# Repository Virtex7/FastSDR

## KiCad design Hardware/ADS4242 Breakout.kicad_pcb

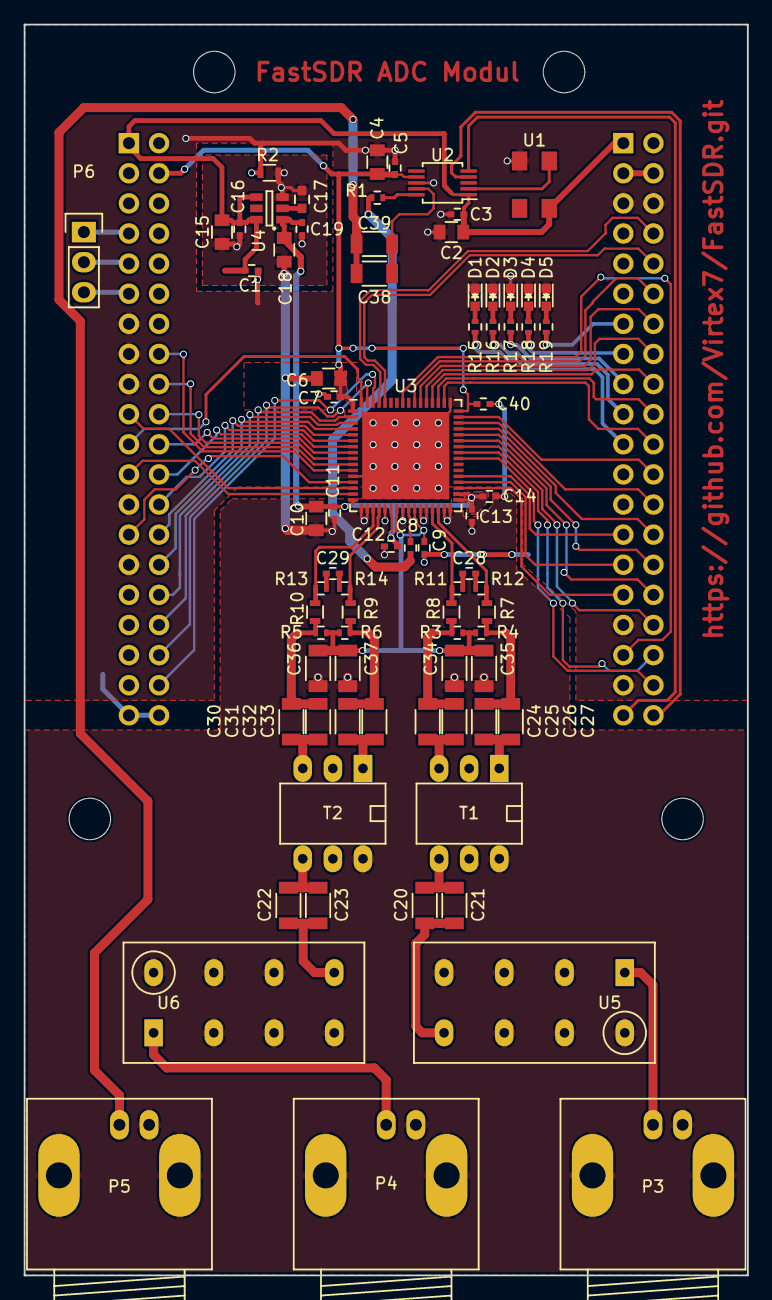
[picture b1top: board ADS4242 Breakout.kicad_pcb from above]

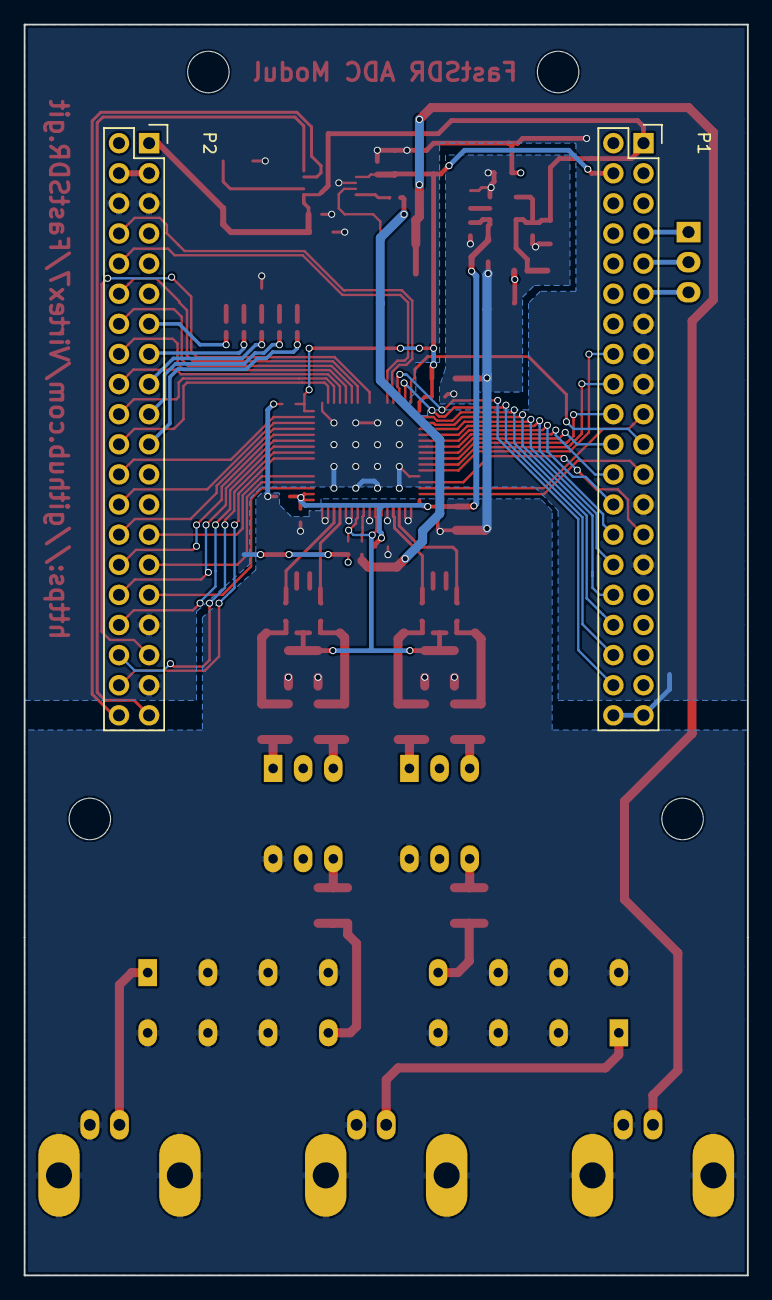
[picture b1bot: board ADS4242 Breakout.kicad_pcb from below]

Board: 2 copper layers, 61.0 x 105.5 mm, 82 parts (2 on the bottom side), 87 nets.

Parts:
C1, C3, C5, C7, C8, C9, C11, C12, C13, C14, C16, C19, C40: 100n; C_0402
C2, C4, C6, C10, C15, C18: 22u; C_0805
C17: 10n; C_0603
C20, C21, C22, C23, C24, C25, C26, C27, C30, C31, C32, C33, C34, C35, C36, C37, C38, C39: 47n; C_1206
C28, C29: 3,3p; C_0402
D1, D2, D3, D4, D5: LED; LED-0603
P1, P2: CONN_02X20; Socket_Strip_Straight_2x20
P3, P4, P5: BNC; BNC_Socket_TYCO-AMP_LargePads
P6: CONN_01X03; Pin_Header_Straight_1x03
P7, P8, P9, P10: CONN_01X01; MountingHole_3-5mm
R1: 49,9; R_0402
R2: 0; R_0603
R3, R4, R5, R6, R11, R12, R13, R14: 25; R_0402
R7, R8, R9, R10: 15; R_0603
R15, R16, R17, R18, R19: 1k; R_0402
T1, T2: T1-1T-X65; DIP-6__300_ELL
U1: FOX924B; FOX924
U2: SI5351A3; MSOP-10_3x3mm_Pitch0.5mm
U3: ADS4242; QFN-64-1EP_9x9mm_Pitch0.5mm
U4: TPS734xxDRV; SOT-23-6
U5, U6: PLP-21.4; A01-8

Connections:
1,8V: C4.1, C5.1, C6.1, C7.1, C40.1, P1.4, U2.7, U3.1, U3.48
3,3V: C1.1, C2.1, C3.1, C15.1, C16.1, P1.1, P2.1, U1.4, U2.1, U4.4, U4.6
5V: P2.3, P2.4
/CTL00: P2.31, U3.35
/CTL01: P2.29, U3.36
/CTL02: P2.27, U3.37
/CTL05: P2.21, R15.1
/CTL06: P2.19, R16.1
/CTL07: P2.17, R17.1
/CTL08: P2.15, R18.1
/CTL09: P2.13, R19.1
/DQ00: P2.38, U3.40
/DQ01: P2.36, U3.41
/DQ02: P2.34, U3.42
/DQ03: P2.32, U3.43
/DQ04: P2.30, U3.44
/DQ05: P2.28, U3.45
/DQ06: P2.26, U3.46
/DQ07: P2.24, U3.47
/DQ08: P2.22, U3.50
/DQ09: P2.20, U3.51
/DQ10: P2.18, U3.52
/DQ11: P2.16, U3.53
/DQ12: P2.14, U3.54
/DQ13: P2.12, U3.55
/DQ14: P2.10, U3.60
/DQ15: P2.8, U3.61
/DQ16: P1.38, U3.62
/DQ17: P1.36, U3.63
/DQ18: P1.34, U3.2
/DQ19: P1.32, U3.3
/DQ20: P1.30, U3.4
/DQ21: P1.28, U3.5
/DQ22: P1.26, U3.6
/DQ23: P1.24, U3.7
/DQ24: P1.22, U3.8
/DQ25: P1.20, U3.9
/DQ26: P1.18, U3.10
/DQ27: P1.16, U3.11
/I²C_SCL_FX3: P2.40, U2.4
/I²C_SDA_FX3: P2.39, U2.5
/PClk: P2.35, U3.57
/PMode_0: P1.11, P6.3
/PMode_1: P1.9, P6.2
/PMode_2: P1.7, P6.1
/Spi-Miso_Uart_TX: P1.21, U3.64
/Spi-Mosi_Uart-RX: P1.19, U3.14
/Spi-Sck_Uart-RTS: P1.27, U3.13
/Spi-Ssn_Uart-CTS: P1.23, U3.15
/VCM: C9.1, C34.1, C35.1, C36.1, C37.1, R3.2, R4.1, R5.2, R6.1, U3.23, U3.26
GND: C1.2, C2.2, C3.2, C4.2, C5.2, C9.2, D1.1, D2.1, D3.1, D4.1, D5.1, P1.13, P1.15, P1.17, P1.25, P1.29, P1.39, P1.40, P2.5, P2.6, P2.33, P2.37, R2.2, U1.2, U2.8, U3.12, U3.49, U3.65
GNDA: C6.2, C7.2, C10.2, C11.2, C12.2, C13.2, C14.2, C15.2, C16.2, C17.2, C18.2, C19.2, C34.2, C35.2, C36.2, C37.2, C40.2, P3.2, P4.2, P5.2, R2.1, T1.6, T2.6, U3.17, U3.18, U3.21, U3.24, U3.27, U3.28, U3.31, U3.32, U4.3, U5.2, U5.3, U5.4, U5.5, U5.6, U5.7, U6.2, U6.3, U6.4, U6.5, U6.6, U6.7
unnamed: C8.1, R1.1
unnamed: C8.2, U3.25
unnamed: C17.1, U4.2
unnamed: C20.1, C21.1, U5.8
unnamed: C20.2, C21.2, T1.4
unnamed: C22.1, C23.1, U6.8
unnamed: C22.2, C23.2, T2.4
unnamed: C24.1, C25.1, T1.3
unnamed: C24.2, C25.2, R3.1, R7.2
unnamed: C26.1, C27.1, T1.1
unnamed: C26.2, C27.2, R4.2, R8.1
unnamed: C28.1, R11.2
unnamed: C28.2, R12.1
unnamed: C29.1, R13.2
unnamed: C29.2, R14.1
unnamed: C30.1, C31.1, T2.3
unnamed: C30.2, C31.2, R5.1, R9.2
unnamed: C32.1, C33.1, T2.1
unnamed: C32.2, C33.2, R6.2, R10.1
unnamed: C38.1, C39.1, U2.9
unnamed: C38.2, C39.2, P5.1
unnamed: D1.2, R15.2
unnamed: D2.2, R16.2
unnamed: D3.2, R17.2
unnamed: D4.2, R18.2
unnamed: D5.2, R19.2
unnamed: P3.1, U5.1
unnamed: P4.1, U6.1
unnamed: R1.2, U2.10
unnamed: R10.2, R14.2, U3.20
unnamed: R7.1, R11.1, U3.29
unnamed: R8.2, R12.2, U3.30
unnamed: R9.1, R13.1, U3.19
unnamed: U1.3, U2.2
VAA: C10.1, C11.1, C12.1, C13.1, C14.1, C18.1, C19.1, U3.16, U3.22, U3.33, U3.34, U4.1

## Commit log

2015-07-30 inital commit
2015-08-07 Layout fertig.
